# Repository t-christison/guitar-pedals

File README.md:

<!--
Comments
-->

## Overview

## Pedals

### Tube Screamer

The Ibanez Tube Screamer is an overdrive pedal first released in the late 1970s. The pedal is widely used and often associated with players such as Stevie Ray Vaughan, John Mayer, Mike McCready, and Trey Anastasio, among others. The Tube Screamer's "Drive", "Tone", and "Level" knobs adjust the gain, treble, and output volume of the pedal, respectively. 

The effects alter the instrument sound by clipping the signal (pushing it past its maximum, which shears off the peaks and troughs of the signal waves), adding sustain and harmonic and inharmonic overtones and leading to a compressed sound that is often described as "warm" and "dirty", depending on the type and intensity of distortion used. The terms distortion and overdrive are often used interchangeably; where a distinction is made, distortion is a more extreme version of the effect than overdrive. 

Popular versions of the pedal include:
* TS808
* TS9
* TS10

The Tube Screamer overdrive is produced using two silicon diodes in anti-parallel arrangement into the negative feedback circuit of an operational amplifier ("op-amp") circuit, to produce soft, symmetrical distortion of the input waveform. When the output exceeds the forward volt drop of the diodes the amplifier gain is much lower, effectively limiting the output to + and - one diode volt-drop, although due to the exponential I-V curve of the diodes this is not a hard limit. A "drive" potentiomenter in the feedback path provides variable gain.

Much has been made of the operational amplifier chips used in the various versions of the Tube Screamer pedal, and several "fairy tales" about the merits of these devices have been written on the subject. The JRC4558D chip is well-regarded by some. In reality, the type of op-amp has little to do with the sound of the pedal, which is dominated by the diodes in the op-amp's feedback path.

### Big Muff Pi

The Electro-Harmonix Big Muff Pi

A fuzz pedal or "fuzzbox" is a type of overdrive pedal that clips a sound-wave until it is nearly a squarewave, resulting in a heavily distorted or "fuzzy" sound.

### Dyna Comp 

One of the most popular compressors of all time. Produced by MXR since the 1970s, the pedal produces a dynamic range compression effect. The two controls knobs "Output" and "Sensitivity" determine the output level and amount of compression, respectively. 

Dynamic range compression (DRC) or simply compression is an audio signal processing operation that reduces the volume of loud sounds or amplifies quiet sounds, thus reducing or compressing an audio signal's dynamic range. 

### Phase 90

Introduced by MXR in 1972, the Phase 90 was the first pedal launched by the company. Speed knob varies the rate of the phase sweep.  

A phaser is an electronic sound processor used to filter a signal by creating a series of peaks and troughs in the frequency spectrum. The position of the peaks and troughs of the waveform being affected is typically modulated by an internal low-frequency oscillator so that they vary over time, creating a sweeping effect. Phasers fall under the category of modulation effects. 

## Notes  
All pedals designs in this project have been designed to used a 3PDT switch to include true bypass and neglect the inclusion of a 9V battery to simplify the wiring and soldering of the pedals.  

## References  
[Electrosmash Circuit Analysis](https://www.electrosmash.com/)  
[Big Muff Pi Circuit Analysis](http://www.bigmuffpage.com/)
[DIY Pedal Etching](https://diy-guitar-effects.tumblr.com/etching)

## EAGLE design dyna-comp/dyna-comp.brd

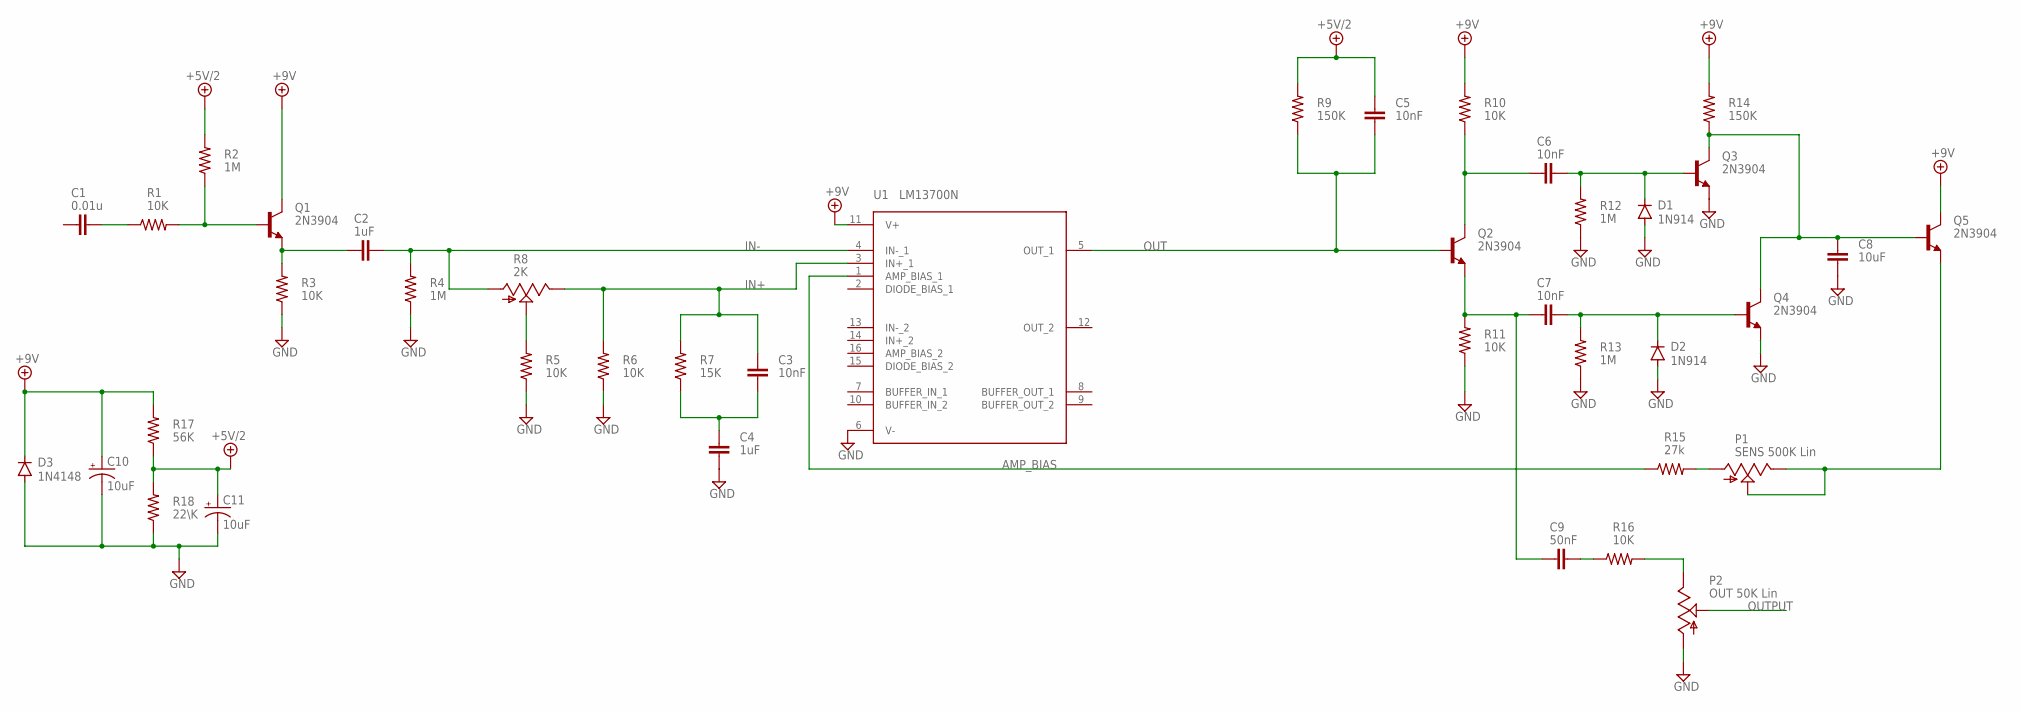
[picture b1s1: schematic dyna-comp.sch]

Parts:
C1: 0.01u; C050-024X044
C2, C4: 1uF; C050-024X044
C3, C5, C6, C7: 10nF; C050-024X044
C8: 10uF; C050-024X044
C9: 50nF; C050-024X044
C10, C11: 10uF; TT2D5
D1, D2: 1N914; DO35-7
D3: 1N4148; DO35-7
P1: SENS 500K Lin; POT-5.08MM
P2: OUT 50K Lin; POT-5.08MM
Q1, Q2, Q3, Q4, Q5: 2N3904; TO92
R1, R3, R5, R6, R10, R11, R16: 10K; 0309/12
R2, R4, R12, R13: 1M; 0309/12
R7: 15K; 0309/12
R8: 2K; CA6V
R9, R14: 150K; 0309/12
R15: 27k; 0309/12
R17: 56K; 0309/12
R18: 22\K; 0309/12
U1: LM13700N; DIL16

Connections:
+5V/2: C5.1, C11.+, R2.2, R9.2, R17.1, R18.2
+9V: C10.+, D3.C, Q1.3 (C), Q5.3 (C), R10.2, R14.2, R17.2, U1.11 (V+)
AMP_BIAS: R15.1, U1.1 (AMP_BIAS_1)
GND: C4.2, C8.2, C10.-, C11.-, D1.A, D2.A, D3.A, P2.1, Q3.1 (E), Q4.1 (E), R3.1, R4.1, R5.1, R6.1, R11.1, R12.1, R13.1, R18.1, U1.6 (V-)
IN+: C3.1, R6.2, R7.2, R8.E, U1.3 (IN+_1)
IN-: C2.2, R4.2, R8.A, U1.4 (IN-_1)
unnamed: C1.2, R1.1
unnamed: Q1.2 (B), R1.2, R2.1
unnamed: C6.1, Q2.3 (C), R10.1
unnamed: C2.1, Q1.1 (E), R3.2
unnamed: R5.2, R8.S
unnamed: C7.1, C9.1, Q2.1 (E), R11.2
unnamed: C6.2, D1.C, Q3.2 (B), R12.2
unnamed: C3.2, C4.1, R7.1
unnamed: C7.2, D2.C, Q4.2 (B), R13.2
unnamed: P1.2, P1.3, Q5.1 (E)
unnamed: C8.1, Q3.3 (C), Q4.3 (C), Q5.2 (B), R14.1
unnamed: P1.1, R15.2
unnamed: P2.3, R16.2
unnamed: C9.2, R16.1
OUT: C5.2, Q2.2 (B), R9.1, U1.5 (OUT_1)
OUTPUT: P2.2

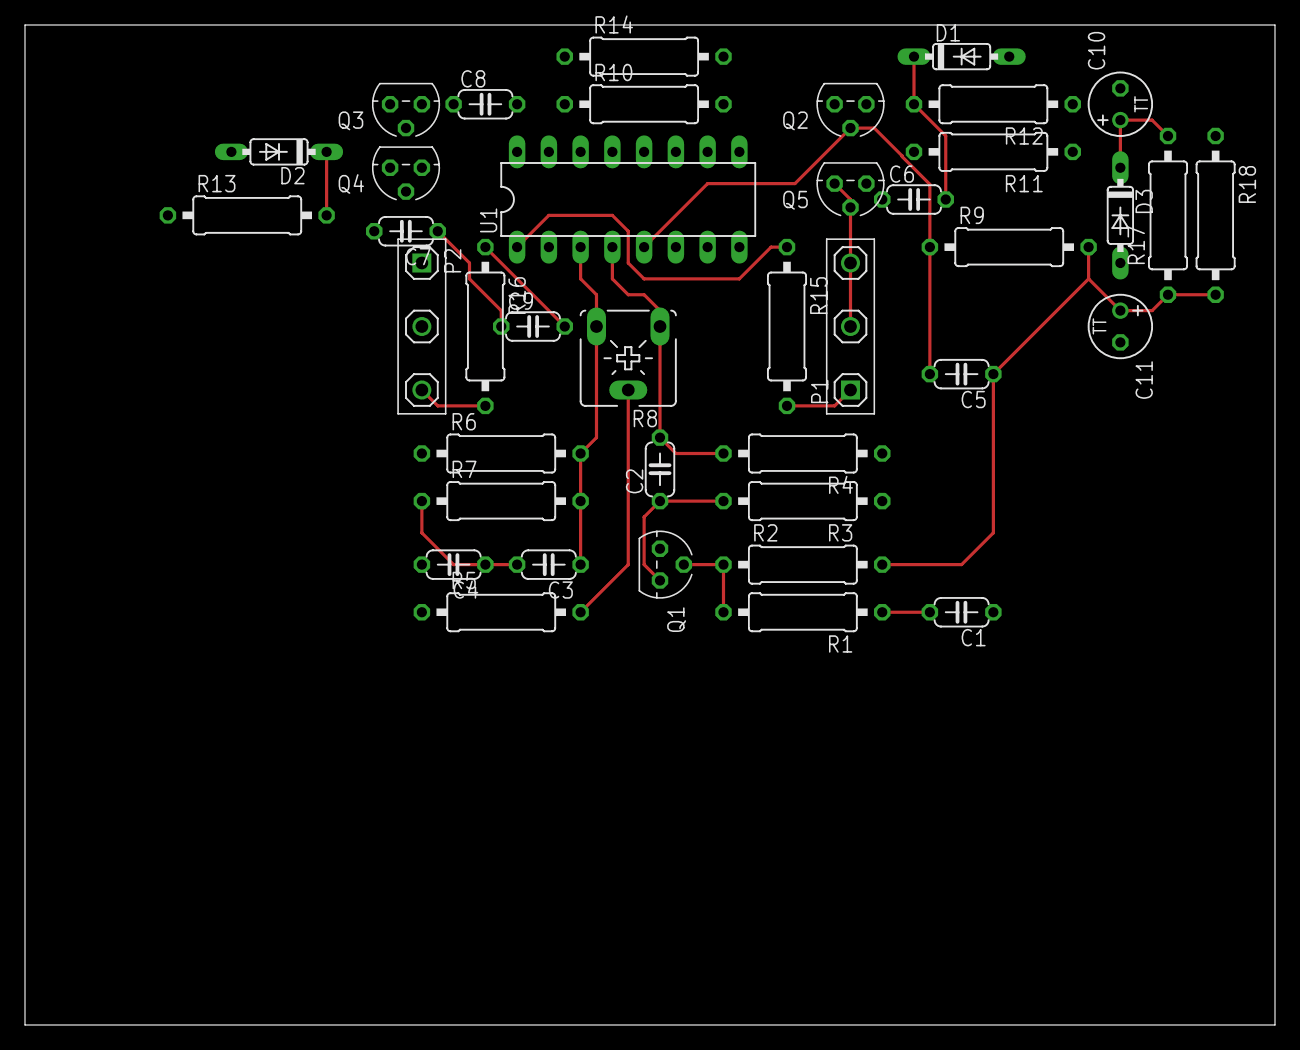
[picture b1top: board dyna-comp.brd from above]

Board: 2 copper layers, 100.0 x 80.0 mm, 40 parts (0 on the bottom side), 21 nets.

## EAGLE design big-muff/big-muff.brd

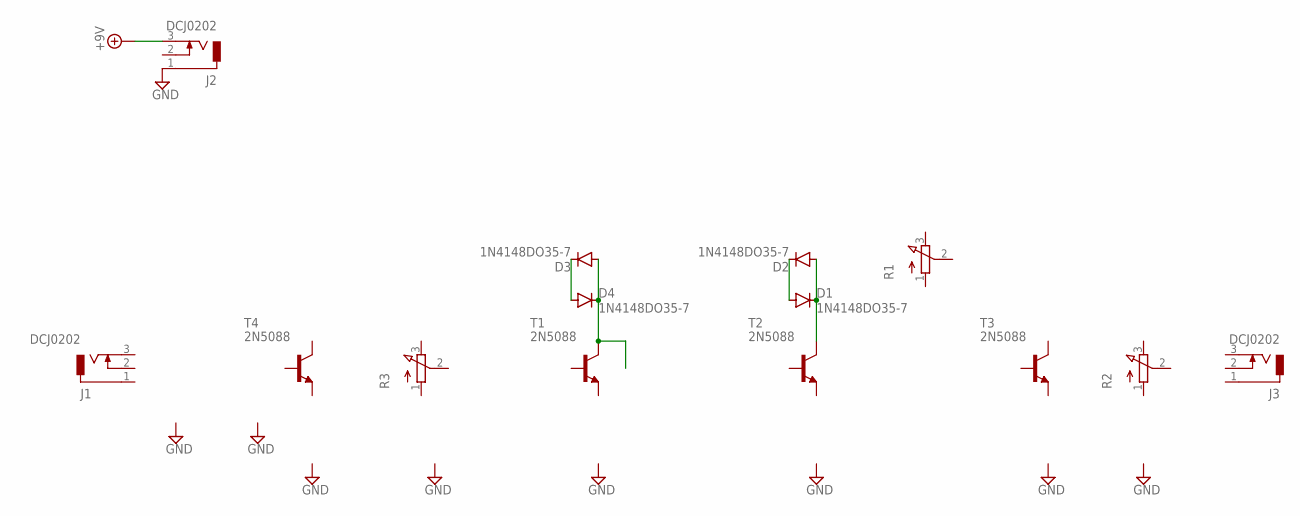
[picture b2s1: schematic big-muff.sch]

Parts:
D1, D2, D3, D4: 1N4148DO35-7; DO35-7
J1, J2, J3: DCJ0202
R1, R2, R3: 3RP/1610N
T1, T2, T3, T4: 2N5088; TO92

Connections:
+9V: J2.3
GND: J2.1
unnamed: D3.A, D4.C, T1.1 (C)
unnamed: D3.C, D4.A
unnamed: D1.A, D2.C
unnamed: D1.C, D2.A, T2.1 (C)

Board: 2 copper layers, 14 parts (0 on the bottom side), 4 nets, no tracks yet.

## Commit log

2021-05-05 Added schematic references and BOM
2021-05-05 added images for readme
2021-05-05 Added images to readme
2021-05-05 update to image tags in readme
2021-05-05 added references to readme
2021-05-05 Formatting newlines
2021-05-05 Header formatting
2021-05-05 Updates to readme
2021-05-06 made initial changes for big muff
2021-12-27 schematics for dyna-comp, phase-90, and tube-screamer
